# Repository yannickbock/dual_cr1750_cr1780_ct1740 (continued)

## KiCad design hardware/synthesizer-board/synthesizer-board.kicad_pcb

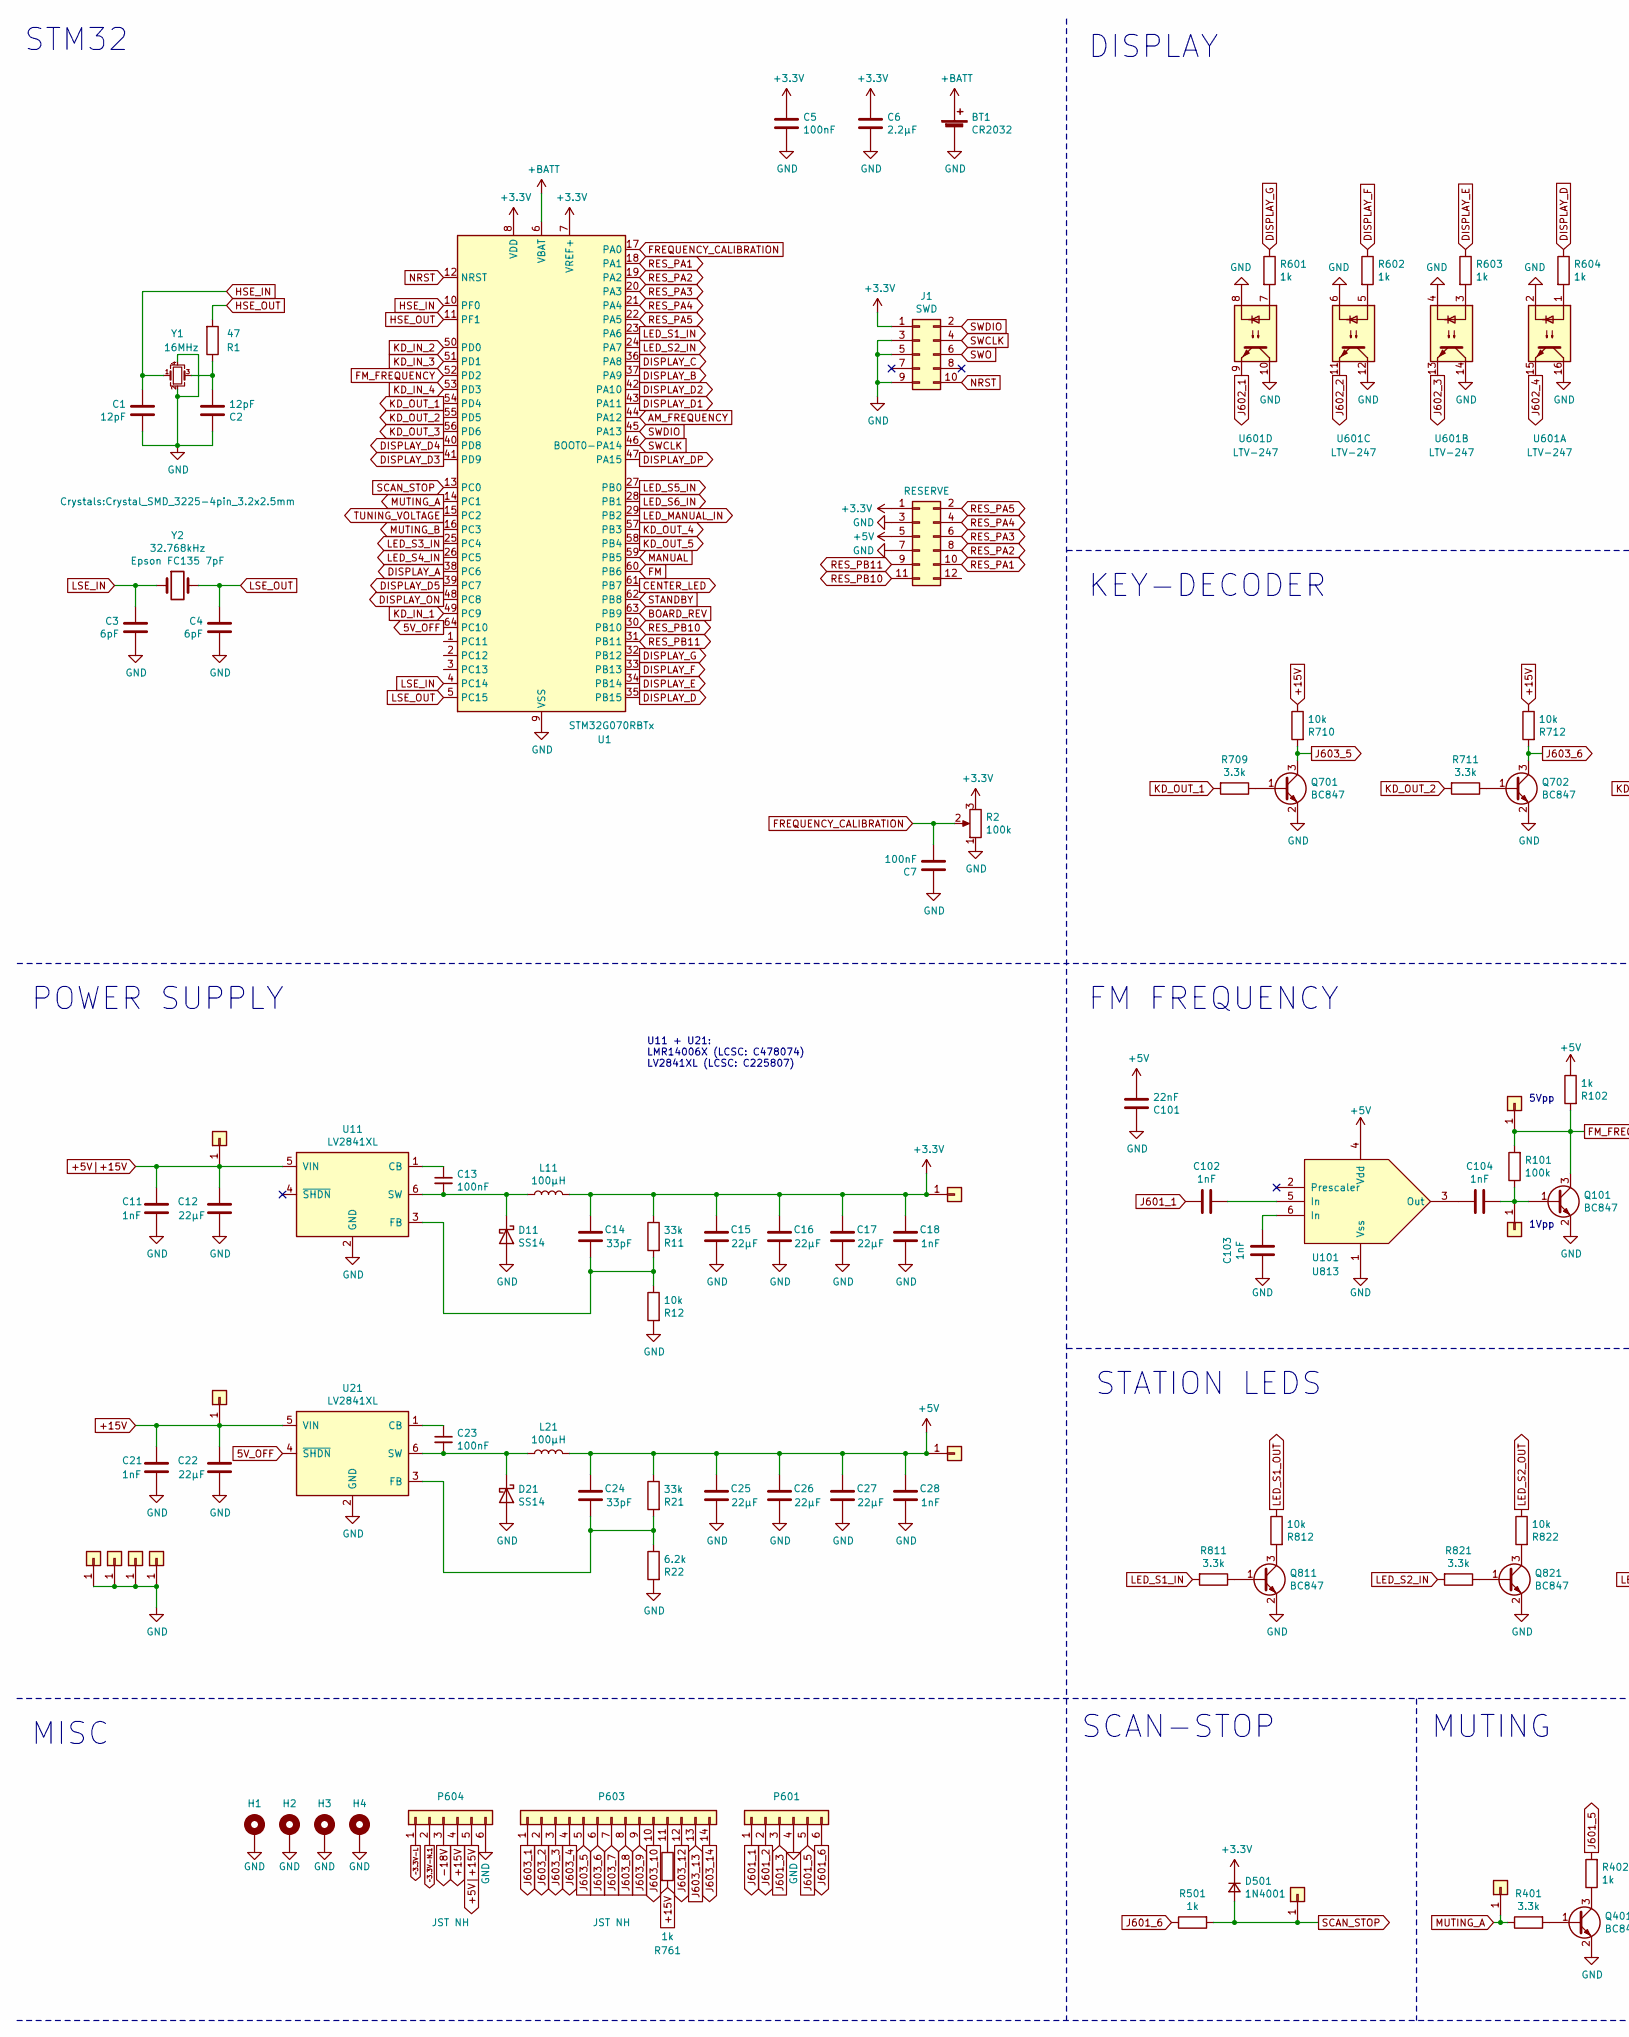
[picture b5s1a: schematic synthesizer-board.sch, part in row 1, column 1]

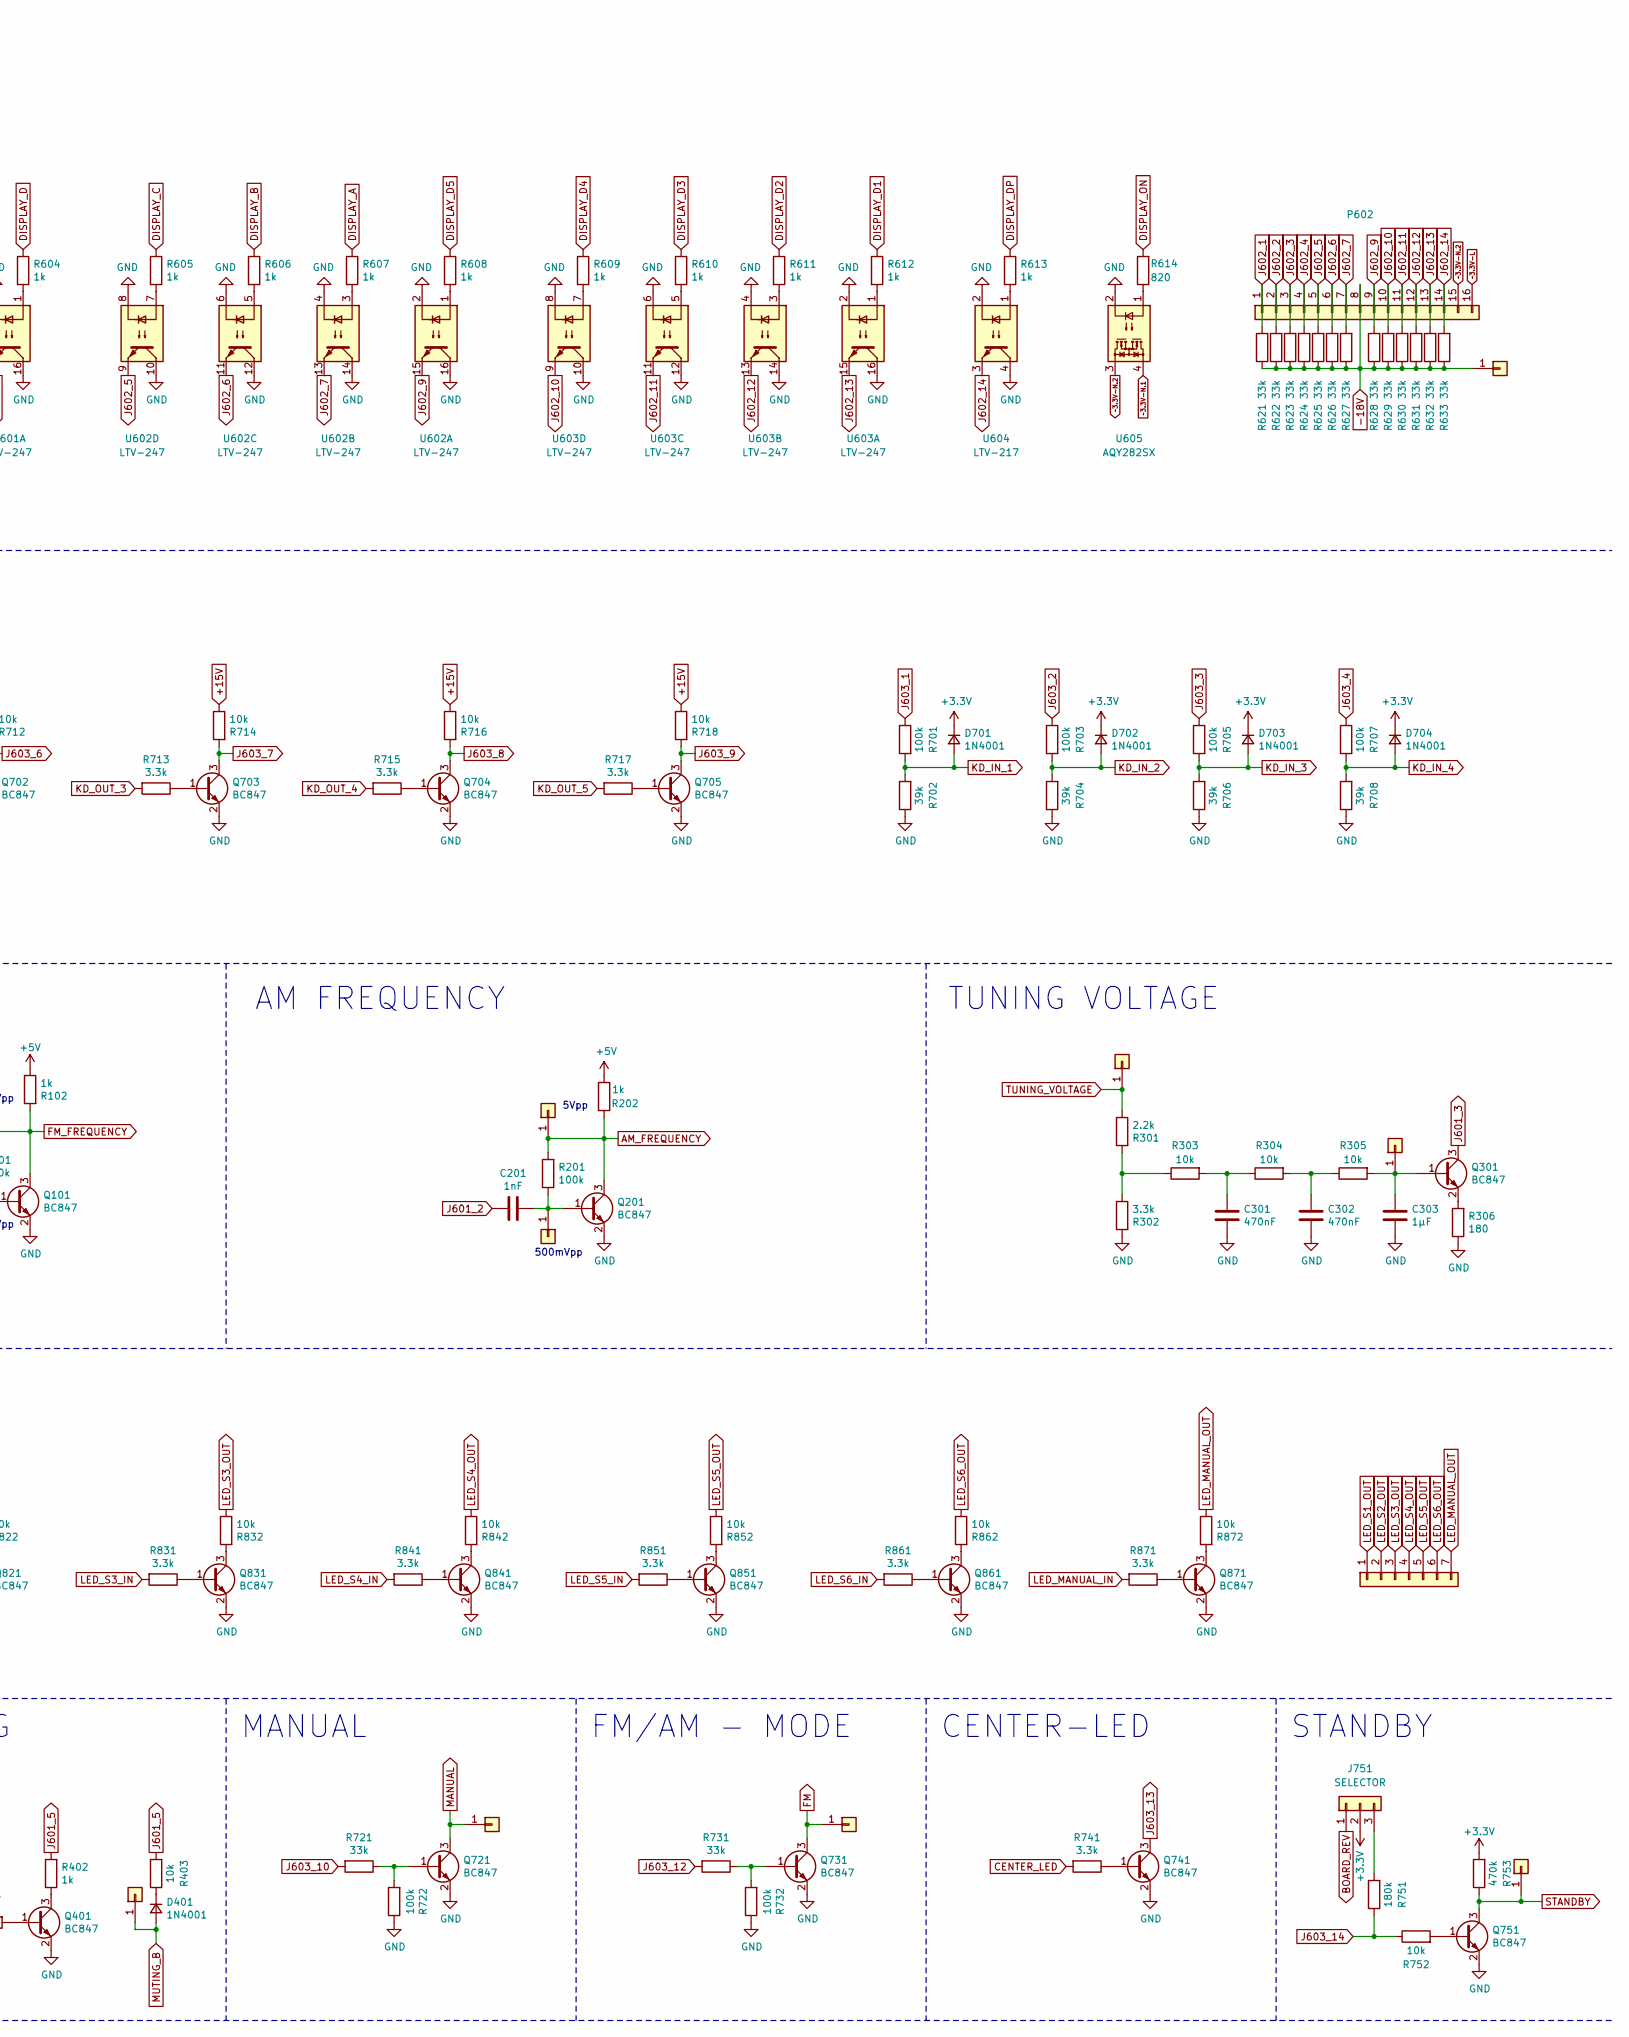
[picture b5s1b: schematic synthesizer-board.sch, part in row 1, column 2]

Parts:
BT1: CR2032; Keystone_103_1x20mm-CoinCell
C1, C2: 12pF; C_0805; LCSC C1804
C3, C4: 6pF; C_0805; LCSC C67560
C5, C7, C13, C23: 100nF; C_0805; LCSC C49678
C6: 2.2µF; C_0805; LCSC C49217
C11, C18, C21, C28, C102, C103, C104, C201: 1nF; C_0805; LCSC C46653
C12, C15, C16, C17, C22, C25, C26, C27: 22µF; C_0805; LCSC C45783
C14, C24: 33pF; C_0805; LCSC C1814
C101: 22nF; C_0805; LCSC C1729
C301, C302: 470nF; C_0805; LCSC C13967
C303: 1µF; C_0805; LCSC C28323
D11, D21: SS14; D_SMA; LCSC C2480
D401, D501, D701, D702, D703, D704: 1N4001; D_SOD-123F; LCSC C64898
H1, H2, H3, H4: MountingHole_Pad; MountingHole_5mm_Pad_Via
J1: SWD; Pin_Header_Straight_2x05_Pitch2.54mm
J2, J3, J5, J6, J7, J8, J9, J10, J11, J12, J13, J14, J15, J16, J17, J18, J19, J20, J21, J22, J23: Conn_01x01; Measurement_Point_Round-TH_Small
J4: Conn_01x07; JST_XH_B07B-XH-A_07x2.50mm_Straight
J24: RESERVE; Pin_Header_Straight_2x06_Pitch2.54mm
J751: SELECTOR; Pin_Header_Straight_1x03_Pitch2.54mm
L11, L21: 100µH; BCNR6045CF1-101M; LCSC C238004
P601: Conn_01x06_Male; Conn_5.0_3.5_x6
P602: Conn_01x16_Male; JST_XH_B16B-XH-A_16x2.50mm_Straight
P603: JST NH; JST_XH_B14B-XH-A_14x2.50mm_Straight
P604: JST NH; JST_XH_B06B-XH-A_06x2.50mm_Straight
Q101, Q201, Q301, Q701, Q702, Q703, Q704, Q705, Q721, Q731, Q741, Q751, Q811, Q821, Q831, Q841, Q851, Q861, Q871: BC847; SOT-23; LCSC C2145
Q401: BC847; SOT-23
R1: 47; R_0603; LCSC C23182
R2: 100k; Potentiometer_Trimmer_Bourns_3296W
R11, R21, R621, R622, R623, R624, R625, R626, R627, R628, R629, R630, R631, R632, R633, R721, R731: 33k; R_0805; LCSC C17633
R12, R303, R304, R305, R403, R710, R712, R714, R716, R718, R752, R812, R822, R832, R842, R852, R862, R872: 10k; R_0805; LCSC C17414
R22: 6.2k; R_0805; LCSC C17767
R101, R201, R701, R703, R705, R707, R722, R732: 100k; R_0805; LCSC C17407
R102, R202, R402, R501, R601, R602, R603, R604, R605, R606, R607, R608, R609, R610, R611, R612, R613: 1k; R_0805; LCSC C17513
R301: 2.2k; R_0805; LCSC C17520
R302, R401, R709, R711, R713, R715, R717, R741, R811, R821, R831, R841, R851, R861, R871: 3.3k; R_0805; LCSC C26010
R306: 180; R_0805; LCSC C25270
R614: 820; R_0805; LCSC C17837
R702, R704, R706, R708: 39k; R_0805; LCSC C25826
R751: 180k; R_0805; LCSC C17501
R753: 470k; R_0805; LCSC C17709
R761: 1k; R_1206; LCSC C4410
U1: STM32G070RBTx; LQFP-64_10x10mm_Pitch0.5mm; LCSC C529340
U11, U21: LV2841XL; TSOT-23-6; LCSC C225807
U101: U813; R_Array_SIP6
U601, U602, U603: LTV-247; SOP-16_4.4x10.4mm_Pitch1.27mm; LCSC C115451
U604: LTV-217; SOP-4_4.4x2.8mm_Pitch1.27mm; LCSC C691224
U605: AQY282SX; SOP-4_3.8x4.1mm_Pitch2.54mm; LCSC C250827
Y1: 16MHz; Crystal_SMD_3225-4pin_3.2x2.5mm; LCSC C13738
Y2: 32.768kHz; Crystal_SMD_3215-2pin_3.2x1.5mm; LCSC C48615

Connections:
5V_OFF: U1.64 (PC10), U21.4 (~SHDN)
+3V3: C5.2, C6.2, C14.1, C15.1, C16.1, C17.1, C18.1, D501.1 (K), D701.1 (K), D702.1 (K), D703.1 (K), D704.1 (K), J1.1, J2.1, J24.1, J751.2, L11.2, R2.3, R11.1, R753.2, U1.7 (VREF+), U1.8 (VDD)
+5V: C24.1, C25.1, C26.1, C27.1, C28.1, C101.1, J3.1, J24.5, L21.2, R21.1, R102.1, R202.1, U101.4 (Vdd)
+5V|+15V: C11.2, C12.1, J5.1, P604.5, U11.5 (VIN)
+15V: C21.2, C22.1, J6.1, P604.4, R710.1, R712.1, R714.1, R716.1, R718.1, R761.2, U21.5 (VIN)
+BATT: BT1.1 (+), U1.6 (VBAT)
-18V: J15.1, P602.8, P604.3, R621.1, R622.1, R623.1, R624.1, R625.1, R626.1, R627.1, R628.1, R629.1, R630.1, R631.1, R632.1, R633.1
AM_FREQUENCY: J12.1, Q201.3 (C), R201.2, R202.2, U1.44 (PA12)
BOARD_REV: J751.1, U1.63 (PB9)
CENTER_LED: R741.2, U1.61 (PB7)
DISPLAY_A: R607.1, U1.38 (PC6)
DISPLAY_B: R606.1, U1.37 (PA9)
DISPLAY_C: R605.1, U1.36 (PA8)
DISPLAY_D: R604.1, U1.35 (PB15)
DISPLAY_D1: R612.1, U1.43 (PA11)
DISPLAY_D2: R611.1, U1.42 (PA10)
DISPLAY_D3: R610.1, U1.41 (PD9)
DISPLAY_D4: R609.1, U1.40 (PD8)
DISPLAY_D5: R608.1, U1.39 (PC7)
DISPLAY_DP: R613.1, U1.47 (PA15)
DISPLAY_E: R603.1, U1.34 (PB14)
DISPLAY_F: R602.1, U1.33 (PB13)
DISPLAY_G: R601.1, U1.32 (PB12)
DISPLAY_ON: R614.2, U1.48 (PC8)
FM: J22.1, Q731.3 (C), U1.60 (PB6)
FM_FREQUENCY: J11.1, Q101.3 (C), R101.2, R102.2, U1.52 (PD2)
FREQUENCY_CALIBRATION: C7.1, R2.2, U1.17 (PA0)
GND: BT1.2 (-), C1.1, C2.2, C3.1, C4.1, C5.1, C6.1, C7.2, C11.1, C12.2, C15.2, C16.2, C17.2, C18.2, C21.1, C22.2, C25.2, C26.2, C27.2, C28.2, C101.2, C103.2, C301.1, C302.1, C303.1, D11.2 (A), D21.2 (A), H1.1, H2.1, H3.1, H4.1, J1.3, J1.5, J1.9, J7.1, J8.1, J9.1, J10.1, J24.3, J24.7, P601.4, P604.6, Q101.2 (E), Q201.2 (E), Q401.2 (E), Q701.2 (E), Q702.2 (E), Q703.2 (E), Q704.2 (E), Q705.2 (E), Q721.2 (E), Q731.2 (E), Q741.2 (E), Q751.2 (E), Q811.2 (E), Q821.2 (E), Q831.2 (E), Q841.2 (E), Q851.2 (E), Q861.2 (E), Q871.2 (E), R2.1, R12.2, R22.2, R302.2, R306.1, R702.1, R704.1, R706.1, R708.1, R722.1, R732.1, U1.9 (VSS), U11.2 (GND), U21.2 (GND), U101.1 (Vss), U601.2, U601.4, U601.6, U601.8, U601.10, U601.12, U601.14, U601.16, U602.2, U602.4, U602.6, U602.8, U602.10, U602.12, U602.14, U602.16, U603.2, U603.4, U603.6, U603.8, U603.10, U603.12, U603.14, U603.16, U604.2, U604.4, U605.2, Y1.2, Y1.4
HSE_IN: C1.2, U1.10 (PF0), Y1.1
HSE_OUT: R1.2, U1.11 (PF1)
J601_1: C102.2, P601.1
J601_2: C201.1, P601.2
J601_3: P601.3, Q301.3 (C)
J601_5: P601.5, R402.2, R403.2
J601_6: P601.6, R501.1
J602_1: P602.1, R621.2, U601.9
J602_2: P602.2, R622.2, U601.11
J602_3: P602.3, R623.2, U601.13
J602_4: P602.4, R624.2, U601.15
J602_5: P602.5, R625.2, U602.9
J602_6: P602.6, R626.2, U602.11
J602_7: P602.7, R627.2, U602.13
J602_9: P602.9, R628.2, U602.15
J602_10: P602.10, R629.2, U603.9
J602_11: P602.11, R630.2, U603.11
J602_12: P602.12, R631.2, U603.13
J602_13: P602.13, R632.2, U603.15
J602_14: P602.14, R633.2, U604.3
J603_1: P603.1, R701.1
J603_2: P603.2, R703.1
J603_3: P603.3, R705.1
J603_4: P603.4, R707.1
J603_5: P603.5, Q701.3 (C), R710.2
J603_6: P603.6, Q702.3 (C), R712.2
J603_7: P603.7, Q703.3 (C), R714.2
J603_8: P603.8, Q704.3 (C), R716.2
J603_9: P603.9, Q705.3 (C), R718.2
J603_10: P603.10, R721.2
J603_12: P603.12, R731.2
J603_13: P603.13, Q741.3 (C)
J603_14: P603.14, R751.1, R752.1
KD_IN_1: D701.2 (A), R701.2, R702.2, U1.49 (PC9)
KD_IN_2: D702.2 (A), R703.2, R704.2, U1.50 (PD0)
KD_IN_3: D703.2 (A), R705.2, R706.2, U1.51 (PD1)
KD_IN_4: D704.2 (A), R707.2, R708.2, U1.53 (PD3)
KD_OUT_1: R709.2, U1.54 (PD4)
KD_OUT_2: R711.2, U1.55 (PD5)
KD_OUT_3: R713.2, U1.56 (PD6)
KD_OUT_4: R715.2, U1.57 (PB3)
KD_OUT_5: R717.2, U1.58 (PB4)
LED_MANUAL_IN: R871.2, U1.29 (PB2)
LED_MANUAL_OUT: J4.7, R872.1
LED_S1_IN: R811.2, U1.23 (PA6)
LED_S1_OUT: J4.1, R812.1
LED_S2_IN: R821.2, U1.24 (PA7)
LED_S2_OUT: J4.2, R822.1
LED_S3_IN: R831.2, U1.25 (PC4)
LED_S3_OUT: J4.3, R832.1
LED_S4_IN: R841.2, U1.26 (PC5)
LED_S4_OUT: J4.4, R842.1
LED_S5_IN: R851.2, U1.27 (PB0)
LED_S5_OUT: J4.5, R852.1
LED_S6_IN: R861.2, U1.28 (PB1)
LED_S6_OUT: J4.6, R862.1
LSE_IN: C3.2, U1.4 (PC14), Y2.1
LSE_OUT: C4.2, U1.5 (PC15), Y2.2
MANUAL: J21.1, Q721.3 (C), U1.59 (PB5)
MUTING_A: J18.1, R401.1, U1.14 (PC1)
MUTING_B: D401.2 (A), J19.1, U1.16 (PC3)
NRST: J1.10, U1.12 (NRST)
unnamed: C2.1, R1.1, Y1.3
unnamed: C13.1, U11.1 (CB)
unnamed: C13.2, D11.1 (K), L11.1, U11.6 (SW)
unnamed: C14.2, R11.2, R12.1, U11.3 (FB)
unnamed: C23.1, U21.1 (CB)
unnamed: C23.2, D21.1 (K), L21.1, U21.6 (SW)
unnamed: C24.2, R21.2, R22.1, U21.3 (FB)
unnamed: C102.1, U101.5 (In)
unnamed: C103.1, U101.6 (In)
unnamed: C104.1, U101.3 (Out)
unnamed: C104.2, J13.1, Q101.1 (B), R101.1
unnamed: C201.2, J14.1, Q201.1 (B), R201.1
unnamed: C301.2, R303.2, R304.1
unnamed: C302.2, R304.2, R305.1
unnamed: C303.2, J20.1, Q301.1 (B), R305.2
unnamed: D401.1 (K), R403.1
unnamed: J751.3, R751.2
unnamed: P603.11, R761.1
unnamed: Q301.2 (E), R306.2
unnamed: Q401.1 (B), R401.2
unnamed: Q401.3 (C), R402.1
unnamed: Q701.1 (B), R709.1
unnamed: Q702.1 (B), R711.1
unnamed: Q703.1 (B), R713.1
unnamed: Q704.1 (B), R715.1
unnamed: Q705.1 (B), R717.1
unnamed: Q721.1 (B), R721.1, R722.2
unnamed: Q731.1 (B), R731.1, R732.2
unnamed: Q741.1 (B), R741.1
unnamed: Q751.1 (B), R752.2
unnamed: Q811.1 (B), R811.1
unnamed: Q811.3 (C), R812.2
unnamed: Q821.1 (B), R821.1
unnamed: Q821.3 (C), R822.2
unnamed: Q831.1 (B), R831.1
unnamed: Q831.3 (C), R832.2
unnamed: Q841.1 (B), R841.1
unnamed: Q841.3 (C), R842.2
unnamed: Q851.1 (B), R851.1
unnamed: Q851.3 (C), R852.2
unnamed: Q861.1 (B), R861.1
unnamed: Q861.3 (C), R862.2
unnamed: Q871.1 (B), R871.1
unnamed: Q871.3 (C), R872.2
unnamed: R301.2, R302.1, R303.1
unnamed: R601.2, U601.7
unnamed: R602.2, U601.5
unnamed: R603.2, U601.3
unnamed: R604.2, U601.1
unnamed: R605.2, U602.7
unnamed: R606.2, U602.5
unnamed: R607.2, U602.3
unnamed: R608.2, U602.1
unnamed: R609.2, U603.7
unnamed: R610.2, U603.5
unnamed: R611.2, U603.3
unnamed: R612.2, U603.1
unnamed: R613.2, U604.1
unnamed: R614.1, U605.1
RES_PA1: J24.10, U1.18 (PA1)
RES_PA2: J24.8, U1.19 (PA2)
RES_PA3: J24.6, U1.20 (PA3)
RES_PA4: J24.4, U1.21 (PA4)
RES_PA5: J24.2, U1.22 (PA5)
RES_PB10: J24.11, U1.30 (PB10)
RES_PB11: J24.9, U1.31 (PB11)
SCAN_STOP: D501.2 (A), J17.1, R501.2, U1.13 (PC0)
STANDBY: J23.1, Q751.3 (C), R753.1, U1.62 (PB8)
SWCLK: J1.4, U1.46 (BOOT0-PA14)
SWDIO: J1.2, U1.45 (PA13)
SWO: J1.6
TUNING_VOLTAGE: J16.1, R301.1, U1.15 (PC2)
~~3.3V-L: P602.16, P604.1
~~3.3V-N.1: P604.2, U605.4
~~3.3V-N.2: P602.15, U605.3

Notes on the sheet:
DISPLAY
KEY-DECODER
STM32
FM FREQUENCY
TUNING VOLTAGE
POWER SUPPLY
STATION LEDS
MISC
AM FREQUENCY
STANDBY
CENTER-LED
FM/AM - MODE
MANUAL
MUTING
SCAN-STOP
U11 + U21: LMR14006X (LCSC: C478074) LV2841XL (LCSC: C225807)
5Vpp
1Vpp
500mVpp

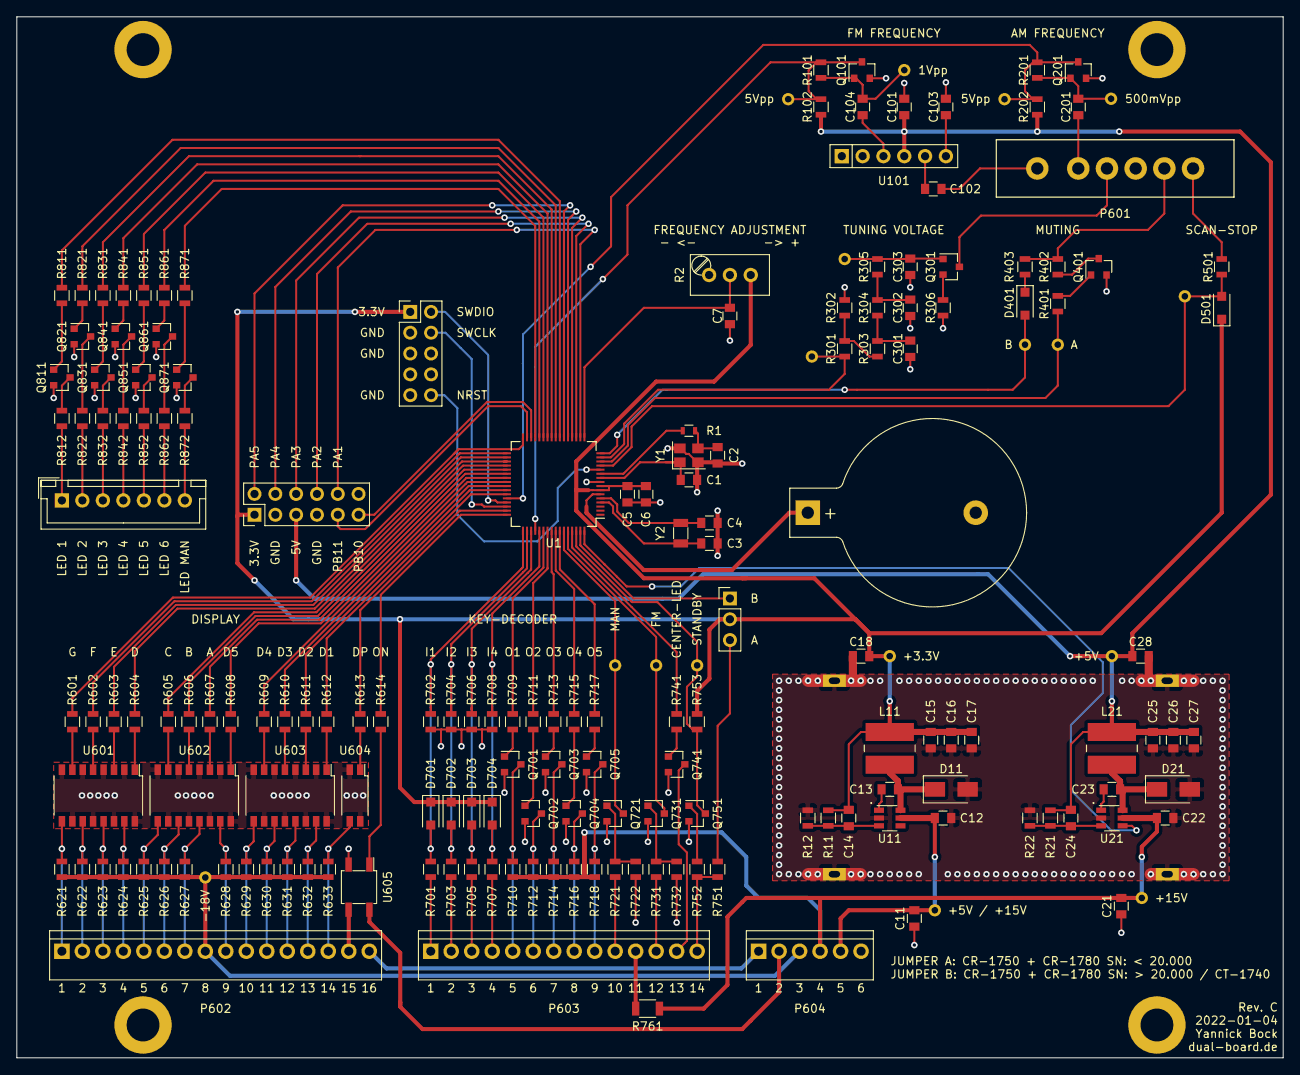
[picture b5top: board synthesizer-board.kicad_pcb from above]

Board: 2 copper layers, 154.5 x 127.0 mm, 194 parts (0 on the bottom side), 164 nets.

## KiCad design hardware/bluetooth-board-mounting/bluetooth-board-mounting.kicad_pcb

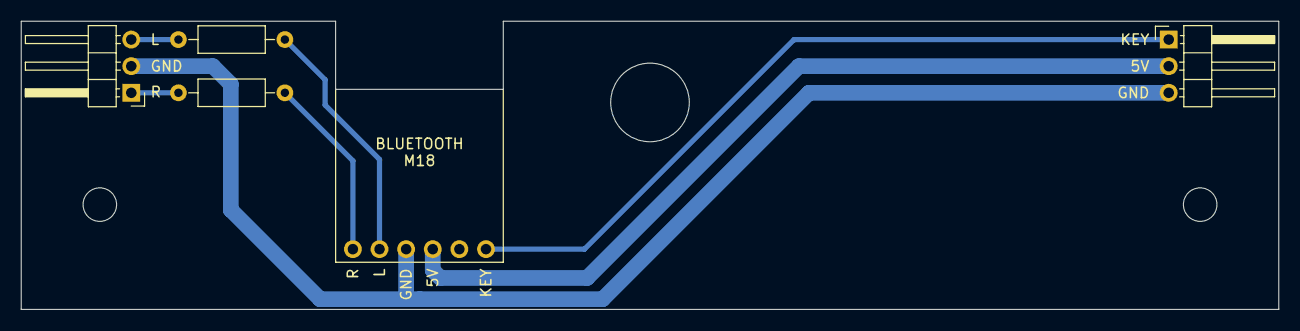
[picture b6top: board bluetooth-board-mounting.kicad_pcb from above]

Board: 2 copper layers, 120.0 x 27.5 mm, 7 parts (0 on the bottom side), 7 nets.

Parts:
H1, H2: MountingHole; MountingHole_3.2mm_M3
J1: Conn_01x06; Pin_Header_Angled_1x03_Pitch2.54mm
J11: Conn_01x03; Pin_Header_Angled_1x03_Pitch2.54mm
R9, R10: 100; R_Axial_DIN0207_L6.3mm_D2.5mm_P10.16mm_Horizontal
U1: BT / M18; Pin_Header_Straight_1x06_Pitch2.54mm

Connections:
+5V: J1.2, U1.4
GND: J1.3, J11.2, U1.3
KEY: J1.1, U1.6
unnamed: R9.2, U1.2
unnamed: R10.2, U1.1
OUT_L: J11.3, R9.1
OUT_R: J11.1, R10.1

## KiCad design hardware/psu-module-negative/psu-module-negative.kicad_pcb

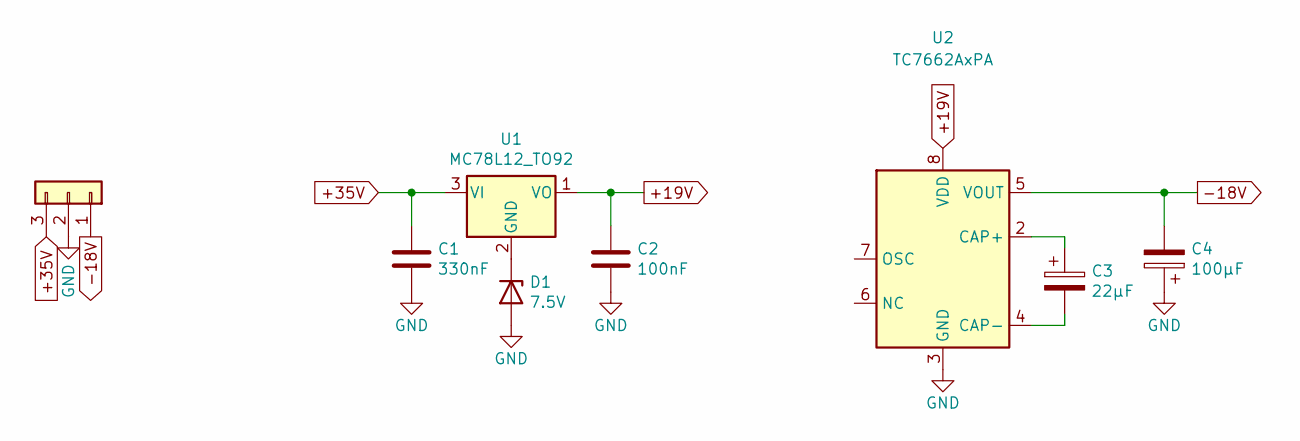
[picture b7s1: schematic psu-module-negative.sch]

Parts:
C1: 330nF; C_Disc_D3.0mm_W2.0mm_P2.50mm
C2: 100nF; C_Disc_D3.0mm_W2.0mm_P2.50mm
C3: 22µF; CP_Radial_D5.0mm_P2.00mm
C4: 100µF; CP_Radial_D6.3mm_P2.50mm
D1: 7.5V; D_DO-35_SOD27_P7.62mm_Horizontal
J1: Conn_01x03; Pin_Header_Angled_1x03_Pitch2.54mm
U1: MC78L12_TO92; TO-92_Molded_Narrow_Oval
U2: TC7662AxPA; DIP-8_W7.62mm

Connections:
+19V: C2.1, U1.1 (VO), U2.8 (VDD)
+35V: C1.1, J1.3, U1.3 (VI)
-18V: C4.2, J1.1, U2.5 (VOUT)
GND: C1.2, C2.2, C4.1, D1.2 (A), J1.2, U2.3 (GND)
unnamed: C3.1, U2.2 (CAP+)
unnamed: C3.2, U2.4 (CAP-)
unnamed: D1.1 (K), U1.2 (GND)

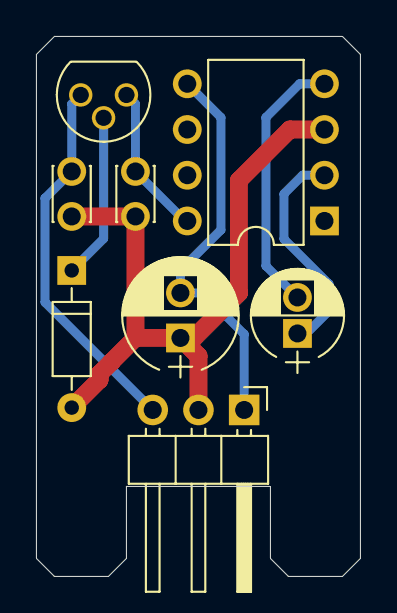
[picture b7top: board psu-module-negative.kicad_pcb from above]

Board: 2 copper layers, 18.0 x 30.0 mm, 8 parts (0 on the bottom side), 7 nets.

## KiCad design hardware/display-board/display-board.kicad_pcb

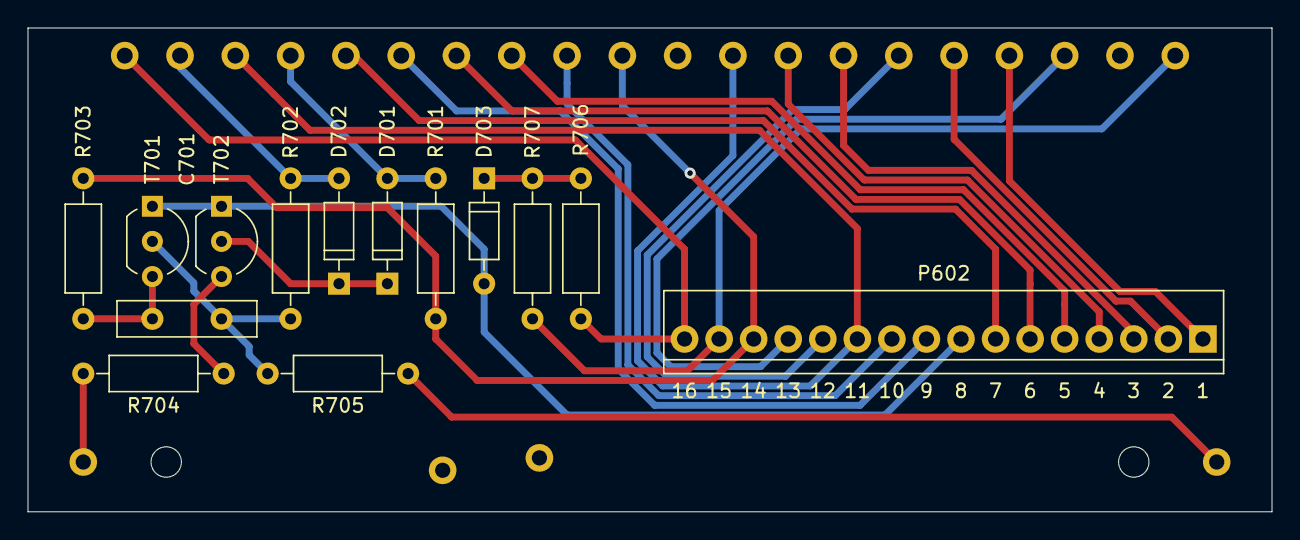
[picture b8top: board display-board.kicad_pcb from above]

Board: 2 copper layers, 90.0 x 35.0 mm, 21 parts (0 on the bottom side), 25 nets.

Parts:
C701: 40nF; C_Disc_D10.0mm_W2.5mm_P5.00mm
D701, D702: IS1588; D_DO-35_SOD27_P7.62mm_Horizontal
D703: HZ4C-3; D_DO-35_SOD27_P7.62mm_Horizontal
H1, H2: MountingHole; MountingHole_2.2mm_M2
J1: Display; DISPLAY_01x20
J2: Conn_01x16
J3: P804_8; SolderWirePad_single_1mmDrill
J4: P804_7; SolderWirePad_single_1mmDrill
J5, J6: Conn_01x01; SolderWirePad_single_1mmDrill
R701, R702: 8,2k; R_Axial_DIN0207_L6.3mm_D2.5mm_P10.16mm_Horizontal
R703, R704: 56k; R_Axial_DIN0207_L6.3mm_D2.5mm_P10.16mm_Horizontal
R705: 5,6k; R_Axial_DIN0207_L6.3mm_D2.5mm_P10.16mm_Horizontal
R706, R707: 560; R_Axial_DIN0207_L6.3mm_D2.5mm_P10.16mm_Horizontal
T701, T702: 2SC945; TO-92_Inline_Wide

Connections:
D1: J1.1, J2.16, R706.1
D2: D702.2, J1.2, R702.2
D4: D701.2, J1.4, R701.1
D5: J1.5, J2.7
D6: J1.6, J2.9
D7: J1.7, J2.6
D8: J1.8, J2.5
D9: J1.9, J2.10
D10: J1.10, J2.14, R701.2, R703.2
D12: J1.3, J1.12, J2.11
D13: J1.13, J2.4
D14: J1.14, J2.3
D15: J1.15, J2.12
D16: J1.16, J2.2
D17: J1.17, J2.1
D18: J1.18, J2.13
D20: J1.20, J2.15, R707.1
unnamed: C701.1, R702.1, R705.2, T701.2
unnamed: C701.2, R703.1, T701.3
unnamed: D701.1, D702.1, T702.2
unnamed: D703.1, R706.2, R707.2
unnamed: J3.1, R704.2
unnamed: J4.1, R705.1
unnamed: R704.1, T702.3
P602_9: D703.2, J2.8, T701.1, T702.1

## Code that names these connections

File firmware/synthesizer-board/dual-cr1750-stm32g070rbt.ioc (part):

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PB13.GPIOParameters=GPIO_Label
PC7.GPIOParameters=GPIO_Label
PA12\ [PA10].GPIO_Label=AM_FREQUENCY
PB14.GPIO_Label=DISPLAY_E
PD3.GPIOParameters=GPIO_Label
PC6.GPIO_Label=DISPLAY_A
PA3.GPIOParameters=GPIO_Label
PA6.GPIO_Label=LED_S1
PB6.GPIO_Label=FM_AM
PD2.GPIOParameters=GPIO_Label
PC15-OSC32_OUT\ (PC15).Mode=LSE-External-Oscillator
PB13.Signal=GPIO_Output
PD6.GPIO_Label=KD_OUT_3
PA2.GPIOParameters=GPIO_Label
PF0-OSC_IN\ (PF0).Signal=RCC_OSC_IN
RCC.SYSCLKSource=RCC_SYSCLKSOURCE_PLLCLK
PC14-OSC32_IN\ (PC14).Mode=LSE-External-Oscillator
PA12\ [PA10].Signal=S_TIM1_ETR
PD4.Signal=GPIO_Output
PB6.Signal=GPIO_Input
PC7.Signal=GPIO_Output
PC3.Signal=GPIO_Output
PD0.Signal=GPIO_Input
PD8.Signal=GPIO_Output
PC1.PinState=GPIO_PIN_SET
PB2.Signal=GPIO_Output
PC1.GPIO_PuPd=GPIO_PULLUP
PD1.GPIOParameters=GPIO_Label
PD1.GPIO_Label=KD_IN_3
PB12.GPIO_Label=DISPLAY_G
PA12\ [PA10].GPIOParameters=GPIO_Label
PB0.GPIOParameters=GPIO_Label
PC4.GPIO_Label=LED_S3
PB1.GPIO_Label=LED_S6
PA0.Mode=IN0
PA8.Signal=GPIO_Output
PA0.Signal=ADC1_IN0
PC8.GPIOParameters=GPIO_Label
Mcu.Package=LQFP64
PB9.Signal=GPIO_Input
PB1.Signal=GPIO_Output
PD5.GPIOParameters=GPIO_Label
PA10.Signal=GPIO_Output
PB9.GPIO_PuPd=GPIO_PULLDOWN
PA5.GPIOParameters=GPIO_Label
PB14.GPIOParameters=GPIO_Label
PB10.GPIOParameters=GPIO_Label
PA4.GPIO_Label=BT_NEXT
PC4.GPIOParameters=PinState,GPIO_PuPd,GPIO_Label
PA6.GPIOParameters=GPIO_Label
PD6.GPIOParameters=GPIO_Label
PD9.GPIO_Label=DISPLAY_D3
PA15.GPIOParameters=GPIO_Label
PC4.PinState=GPIO_PIN_RESET
PA9.GPIO_Label=DISPLAY_B
PB6.GPIO_PuPd=GPIO_PULLUP
PD3.Signal=GPIO_Input
PC6.Signal=GPIO_Output
PC2.Signal=S_TIM15_CH2
PB11.GPIO_Label=BT_DETECTION
PD1.Signal=GPIO_Input
PC0.Signal=GPIO_Input
PF0-OSC_IN\ (PF0).Mode=HSE-External-Oscillator
PC3.GPIOParameters=PinState,GPIO_Label
PB8.GPIO_Label=STANDBY
PA8.GPIO_Label=DISPLAY_C
PA9.Signal=GPIO_Output
PB11.GPIOParameters=GPIO_PuPd,GPIO_Label
PB10.Signal=GPIO_Output
PB14.Signal=GPIO_Output
PA5.Signal=GPIO_Output
PB4.GPIO_Label=KD_OUT_5
PB15.GPIO_Label=DISPLAY_D
PC10.GPIOParameters=GPIO_Label
PA13.Mode=Serial_Wire
PC9.GPIOParameters=GPIO_Label
PC7.GPIO_Label=DISPLAY_D5
PA4.Signal=GPIO_Output
PB5.Signal=GPIO_Input
PF1-OSC_OUT\ (PF1).Signal=RCC_OSC_OUT
PA5.GPIO_Label=BT_PAUSE
PB5.GPIO_PuPd=GPIO_PULLUP
PA0.GPIOParameters=GPIO_Label
PD0.GPIOParameters=GPIO_Label
PC3.GPIO_Label=MUTING_B
PD2.Signal=S_TIM3_ETR
PB0.Signal=GPIO_Output
PA7.GPIOParameters=GPIO_Label
PC1.Signal=GPIO_Output
PB12.GPIOParameters=GPIO_Label
PD2.GPIO_Label=FM_FREQUENCY
Mcu.UserName=STM32G070RBTx
PD9.GPIOParameters=GPIO_Label
PA11\ [PA9].GPIO_Label=DISPLAY_D1
PC10.Signal=GPIO_Output
PA0.GPIO_Label=FREQUENCY_CALIBRATION
PA14-BOOT0.Mode=Serial_Wire
PC0.GPIOParameters=GPIO_PuPd,GPIO_Label
PA9.GPIOParameters=GPIO_Label
PD0.GPIO_Label=KD_IN_2
PC0.GPIO_Label=SCAN_STOP
PB0.GPIO_Label=LED_S5
PB11.GPIO_PuPd=GPIO_PULLUP
PB13.GPIO_Label=DISPLAY_F
PB11.Signal=GPIO_Input
PB15.Signal=GPIO_Output
PC3.PinState=GPIO_PIN_SET
PB5.GPIOParameters=GPIO_PuPd,GPIO_Label
PA15.GPIO_Label=DISPLAY_DP
PB4.GPIOParameters=GPIO_Label
PC1.GPIOParameters=PinState,GPIO_PuPd,GPIO_Label,GPIO_ModeDefaultOutputPP
PD8.GPIOParameters=GPIO_Label
PA8.GPIOParameters=GPIO_Label
PA14-BOOT0.Signal=SYS_SWCLK
RCC.HSE_VALUE=16000000
PA11\ [PA9].GPIOParameters=GPIO_Label
PA10.GPIO_Label=DISPLAY_D2
PB3.GPIOParameters=GPIO_Label
PB7.Signal=GPIO_Output
PF1-OSC_OUT\ (PF1).Mode=HSE-External-Oscillator
PB6.GPIOParameters=GPIO_PuPd,GPIO_Label
PB7.GPIO_Label=CENTER_LED
PA6.Signal=GPIO_Output
PD5.GPIO_Label=KD_OUT_2
PA2.GPIO_Label=DISPLAY_D6_OFF
PA15.Signal=GPIO_Output
PB5.GPIO_Label=MANUAL
PC5.Signal=GPIO_Output
PD3.GPIO_Label=KD_IN_4
PC0.GPIO_PuPd=GPIO_PULLUP
PD6.Signal=GPIO_Output
PB4.Signal=GPIO_Output
PA3.Signal=GPIO_Output
PB3.GPIO_Label=KD_OUT_4
PB8.GPIOParameters=GPIO_Label
PB9.GPIO_Label=STANDBY_VERSION
PC10.GPIO_Label=DISABLE_5V
PC9.GPIO_Label=KD_IN_1
PC4.GPIO_PuPd=GPIO_NOPULL
PC8.Signal=GPIO_Output
PC4.Signal=GPIO_Output
PD5.Signal=GPIO_Output
PD9.Signal=GPIO_Output
PC15-OSC32_OUT\ (PC15).Signal=RCC_OSC32_OUT
PD8.GPIO_Label=DISPLAY_D4
PB9.GPIOParameters=GPIO_PuPd,GPIO_Label
PC8.GPIO_Label=DISPLAY_ON
PA13.Signal=SYS_SWDIO
PB10.GPIO_Label=BT_ON_OFF
PB7.GPIOParameters=GPIO_Label
PC5.GPIOParameters=GPIO_Label
PB2.GPIOParameters=GPIO_Label
board=custom
PD4.GPIO_Label=KD_OUT_1
PC1.GPIO_Label=MUTING_A
PA10.GPIOParameters=GPIO_Label
PD4.GPIOParameters=GPIO_Label
PA4.GPIOParameters=GPIO_Label
PB15.GPIOParameters=GPIO_Label
Mcu.Name=STM32G070RBTx
PA11\ [PA9].Signal=GPIO_Output
PA2.Signal=GPIO_Output
PB3.Signal=GPIO_Output
RCC.SYSCLKFreq_VALUE=63000000
PA7.GPIO_Label=LED_S2
PC5.GPIO_Label=LED_S4
PC14-OSC32_IN\ (PC14).Signal=RCC_OSC32_IN
PB2.GPIO_Label=LED_MAN
PC6.GPIOParameters=GPIO_Label
PC1.GPIO_ModeDefaultOutputPP=GPIO_MODE_OUTPUT_PP
PB8.Signal=GPIO_Input
PC9.Signal=GPIO_Input
PB12.Signal=GPIO_Output
PA3.GPIO_Label=BT_PREV
PB1.GPIOParameters=GPIO_Label
PA7.Signal=GPIO_Output

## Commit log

2021-11-16 Rev. A
2021-12-21 Rev. B
2022-03-17 Rev. C: Hardware
2022-05-05 Rev. C: Firmware
